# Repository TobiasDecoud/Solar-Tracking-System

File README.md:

# Solar-Tracking-System

Sistema que orienta automáticamente un panel solar hacia el sol a lo largo del día para maximizar la captación de energía.

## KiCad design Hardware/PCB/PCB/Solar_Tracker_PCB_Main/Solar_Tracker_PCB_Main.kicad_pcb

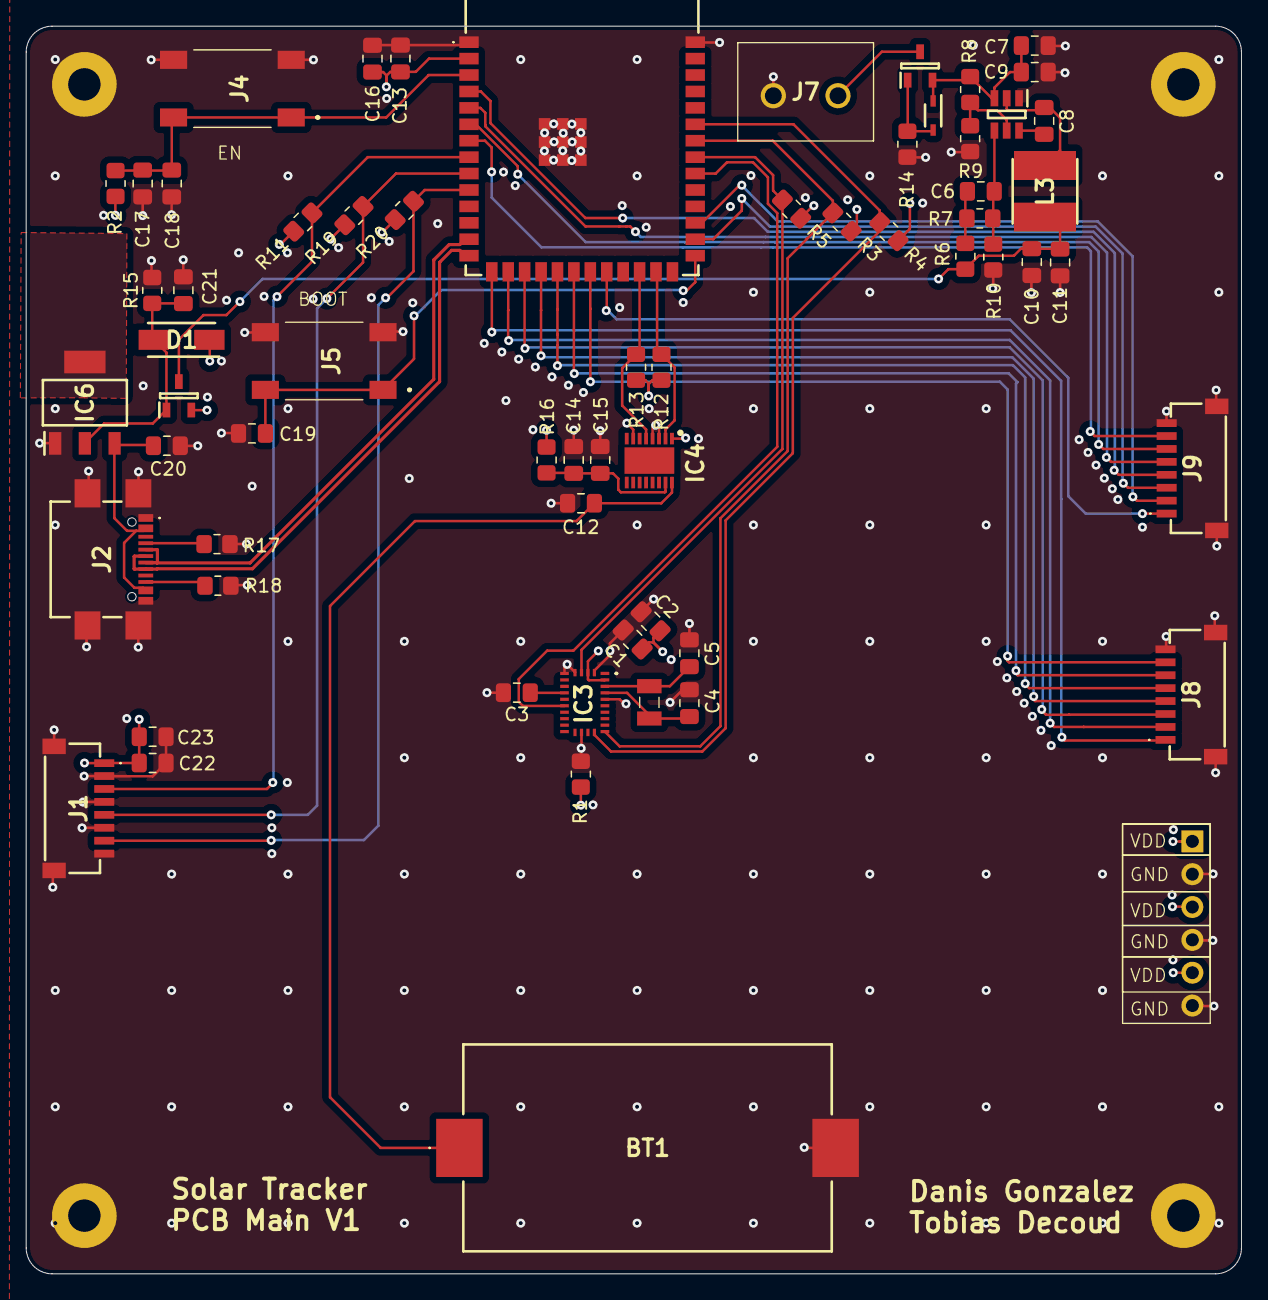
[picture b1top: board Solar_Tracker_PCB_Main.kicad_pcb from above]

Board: 4 copper layers, 94.0 x 96.5 mm, 67 parts (0 on the bottom side), 47 nets.

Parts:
BT1: BAT-HLD-013-SMT-TR; BATHLD013SMTTR
C1, C2, C8, C9, C16, C18, C19: 0.1u; C_0805_2012Metric_Pad1.18x1.45mm_HandSolder
C3, C12, C14, C23: 100n; C_0805_2012Metric_Pad1.18x1.45mm_HandSolder
C4, C5: 22p; C_0805_2012Metric_Pad1.18x1.45mm_HandSolder
C6: 47p; C_0805_2012Metric_Pad1.18x1.45mm_HandSolder
C7, C22: 10u; C_0805_2012Metric_Pad1.18x1.45mm_HandSolder
C10, C11, C13: 22u; C_0805_2012Metric_Pad1.18x1.45mm_HandSolder
C15, C17, C20: 1u; C_0805_2012Metric_Pad1.18x1.45mm_HandSolder
C21: 2.2u; C_0805_2012Metric_Pad1.18x1.45mm_HandSolder
D1: SBR2U30SA-13; DIOM5226X230N
H1, H2, H3, H4: MountingHole_Pad; MountingHole_2.5mm_Pad
IC1: ESP32-S3-WROOM-1-N4R8; ESP32S3WROOM1N4R8
IC2: TPS54302DDCT; SOT95P280X110-6N
IC3: BNO085
IC4: PCF2131TFY; SON50P350X450X150-17N-D
IC6: TLV76133DCYR; SOT230P700X180-4N
J1, J8, J9: SM08B-SRSS-TB_LF__SN_; SM08BSRSSTBLFSN
J2: USB4940-00-A; USB494000A
J3: Conn_01x06_Pin; PinHeader_1x06_P2.54mm_Vertical
J4, J5: 1977223-1; 19772231
J7: TB002-500-02BE; TB00250002BE
L3: 6.8u; INDPM5050X200N
Q1, Q2: DMP2045U-7; SOT96P240X115-3N
R1, R2, R5, R12, R13, R15: 10k; R_0805_2012Metric_Pad1.20x1.40mm_HandSolder
R3, R4: 4k; R_0805_2012Metric_Pad1.20x1.40mm_HandSolder
R6: 49.9; R_0805_2012Metric_Pad1.20x1.40mm_HandSolder
R7, R14: 100k; R_0805_2012Metric_Pad1.20x1.40mm_HandSolder
R8: 511k; R_0805_2012Metric_Pad1.20x1.40mm_HandSolder
R9: 105k; R_0805_2012Metric_Pad1.20x1.40mm_HandSolder
R10: 22.1k; R_0805_2012Metric_Pad1.20x1.40mm_HandSolder
R11, R19, R20: 4.7k; R_0805_2012Metric_Pad1.20x1.40mm_HandSolder
R16: 47k; R_0805_2012Metric_Pad1.20x1.40mm_HandSolder
R17, R18: 5.1k; R_0805_2012Metric_Pad1.20x1.40mm_HandSolder
Y1: 32.768kHz; ABS07
Z1: MM3Z5V6B; SODFL2512X90N

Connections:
+5V: C20.1, IC6.3 (IN), J2.A4 (VBUS_1), J2.B4 (VBUS_2)
/IMU/CAP: C3.1, IC3.9 (CAP)
/IMU/X_IN: C5.1, IC3.27 (XIN32), Y1.1
/IMU/X_OUT: C4.1, IC3.26 (XOUT32/CLKSEL1), Y1.2
/MCU/BOOT: C19.1, IC1.27 (IO0), J5.1 (COM_1), J5.2 (COM_2)
/MCU/EN: C17.1, C18.1, IC1.3 (EN), J4.1 (COM_1), J4.2 (COM_2), R2.2
/RTC/VBAT: BT1.1 (+), C12.2, IC4.16 (VBAT)
/RTC/VDD_IN: C14.2, C15.1, IC4.15 (VDD), R16.2
D+: IC1.14 (IO20), J2.A6 (DP1), J2.B6 (DP2)
D-: IC1.13 (IO19), J2.A7 (DN1), J2.B7 (DN2)
GND: BT1.2 (-), C1.2, C2.2, C3.2, C4.2, C5.2, C7.2, C9.2, C10.2, C11.1, C12.1, C13.2, C14.1, C15.2, C16.2, C17.2, C18.2, C19.2, C20.2, C21.2, C22.2, C23.2, H1.1, H2.1, H3.1, H4.1, IC1.1 (GND_1), IC1.40 (GND_2), IC1.41 (GND_3), IC1.42 (GND_4), IC1.43 (GND_5), IC1.44 (GND_6), IC1.45 (GND_7), IC1.46 (GND_8), IC1.47 (GND_9), IC1.48 (GND_10), IC1.49 (GND_11), IC2.1 (GND), IC3.2 (GND_1), IC3.5 (PS1), IC3.6 (PS0/WAKE), IC3.17 (SA0/H_MOSI_), IC3.25 (GND_2), IC4.3 (SDI), IC4.4 (SDO), IC4.7 (VSS), IC6.1 (GND), J1.2, J1.4, J1.6, J1.8, J1.9 (MP1), J1.10 (MP2), J2.A1 (GND_1), J2.B1 (GND_2), J2.S1 (GND_3), J2.S2 (GND_4), J2.S3 (GND_5), J2.S4 (GND_6), J3.2, J3.4, J3.6, J4.3 (NO_1), J4.4 (NO_2), J5.3 (NO_1), J5.4 (NO_2), J7.1, J8.8, J8.9 (MP1), J8.10 (MP2), J9.8, J9.9 (MP1), J9.10 (MP2), R1.2, R9.2, R10.2, R14.2, R15.2, R17.1, R18.2
IMU_BOOTN: IC1.33 (IO40), IC3.4 (BOOTN), R5.2
IMU_NRST: IC1.32 (IO39), IC3.11 (NRST)
IMU_SCL: IC1.35 (IO42), IC3.19 (H_SCL/SCK/RX), R4.2
IMU_SDA: IC1.34 (IO41), IC3.20 (H_SDA/H_MISO/TX_), R3.2
J1_2: IC1.21 (IO13), J8.7
J1_3: IC1.20 (IO12), J8.6
J1_4: IC1.19 (IO11), J8.5
J1_5: IC1.18 (IO10), J8.4
J1_6: IC1.17 (IO9), J8.3
J1_7: IC1.16 (IO46), J8.2
J1_8: IC1.15 (IO3), J8.1
J6_1: IC1.22 (IO14), J9.1
J6_2: IC1.29 (IO36), J9.2
J6_3: IC1.28 (IO35), J9.3
J6_4: IC1.4 (IO4), J9.4
J6_5: IC1.5 (IO5), J9.5
J6_6: IC1.6 (IO6), J9.6
J6_7: IC1.7 (IO7), J9.7
unnamed: C6.1, R6.2, R7.1
unnamed: C8.2, IC2.6 (BOOT)
unnamed: IC2.5 (EN), R8.2, R9.1
unnamed: C6.2, IC2.4 (FB), R7.2, R10.1
unnamed: C8.1, IC2.2 (SW), L3.1
unnamed: J2.A5 (CC1), R17.2
unnamed: J2.B5 (CC2), R18.1
unnamed: J7.2, Q1.3 (D)
unnamed: Q1.1 (G), R14.1, Z1.2 (A)
RTC_SCL: IC1.25 (IO48), IC4.2 (SCL), R12.2
RTC_SDA: IC1.24 (IO47), IC4.5 (SDA/~CE), R13.2
SL_INT: IC1.10 (IO17), J1.7, R20.2
SL_SCL: IC1.8 (IO15), J1.3, R11.2
SL_SDA: IC1.9 (IO16), J1.5, R19.2
Salida_protegida: C7.1, C9.1, IC2.3 (VIN), Q1.2 (S), R8.1, Z1.1 (K)
VDD: C1.1, C2.1, C13.1, C16.1, C22.1, C23.1, D1.1 (K), IC1.2 (3V3), IC3.3 (VDD), IC3.28 (VDDIO), IC4.1 (IFS), J1.1, J3.1, J3.3, J3.5, Q2.2 (S), R1.1, R2.1, R3.1, R4.1, R5.1, R11.1, R12.1, R13.1, R16.1, R19.1, R20.1
V_BUCK_BORNERA_3V3: C10.1, C11.2, L3.2, Q2.3 (D), R6.1
V_USB_3V3: C21.1, D1.2 (A), IC6.2 (OUT_1), Q2.1 (G), R15.1

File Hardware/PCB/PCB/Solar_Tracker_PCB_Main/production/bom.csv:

Designator,Footprint,Quantity,Value,LCSC Part #
BT1,BATHLD013SMTTR,1,BAT-HLD-013-SMT-TR,
"C1, C16, C18, C19, C2, C8, C9",0805,7,0.1u,
"C10, C11, C13",0805,3,22u,
"C12, C14, C3",0805,3,100n,
"C15, C17, C20",0805,3,1u,
C21,0805,1,2.2u,
"C22, C7",0805,2,10u,
"C4, C5",0805,2,22p,
C6,0805,1,47p,
D1,DIOM5226X230N,1,SBR2U30SA-13,
IC1,ESP32S3WROOM1N4R8,1,ESP32-S3-WROOM-1-N4R8,
IC2,SOT95P280X110-6N,1,TPS54302DDCT,
IC3,BNO085,1,BNO085,
IC4,SON50P350X450X150-17N-D,1,PCF2131TFY,
IC6,SOT230P700X180-4N,1,TLV76133DCYR,
"J1, J8, J9",SM08BSRSSTBLFSN,3,SM08B-SRSS-TB_LF__SN_,
J2,USB494000A,1,USB4940-00-A,
"J4, J5",19772231,2,1977223-1,
J7,TB00250002BE,1,TB002-500-02BE,
L3,INDPM5050X200N,1,6.8u,
"Q1, Q2",SOT96P240X115-3N,2,DMP2045U-7,
"R1, R12, R13, R15, R2, R5",0805,6,10k,
R10,0805,1,22.1k,
"R11, R19, R20",0805,3,4.7k,
"R14, R7",0805,2,100k,
R16,0805,1,47k,
"R17, R18",0805,2,5.1k,
"R3, R4",0805,2,4k,
R6,0805,1,49.9,
R8,0805,1,511k,
R9,0805,1,105k,
Y1,ABS07,1,32.768kHz,
Z1,SODFL2512X90N,1,MM3Z5V6B,

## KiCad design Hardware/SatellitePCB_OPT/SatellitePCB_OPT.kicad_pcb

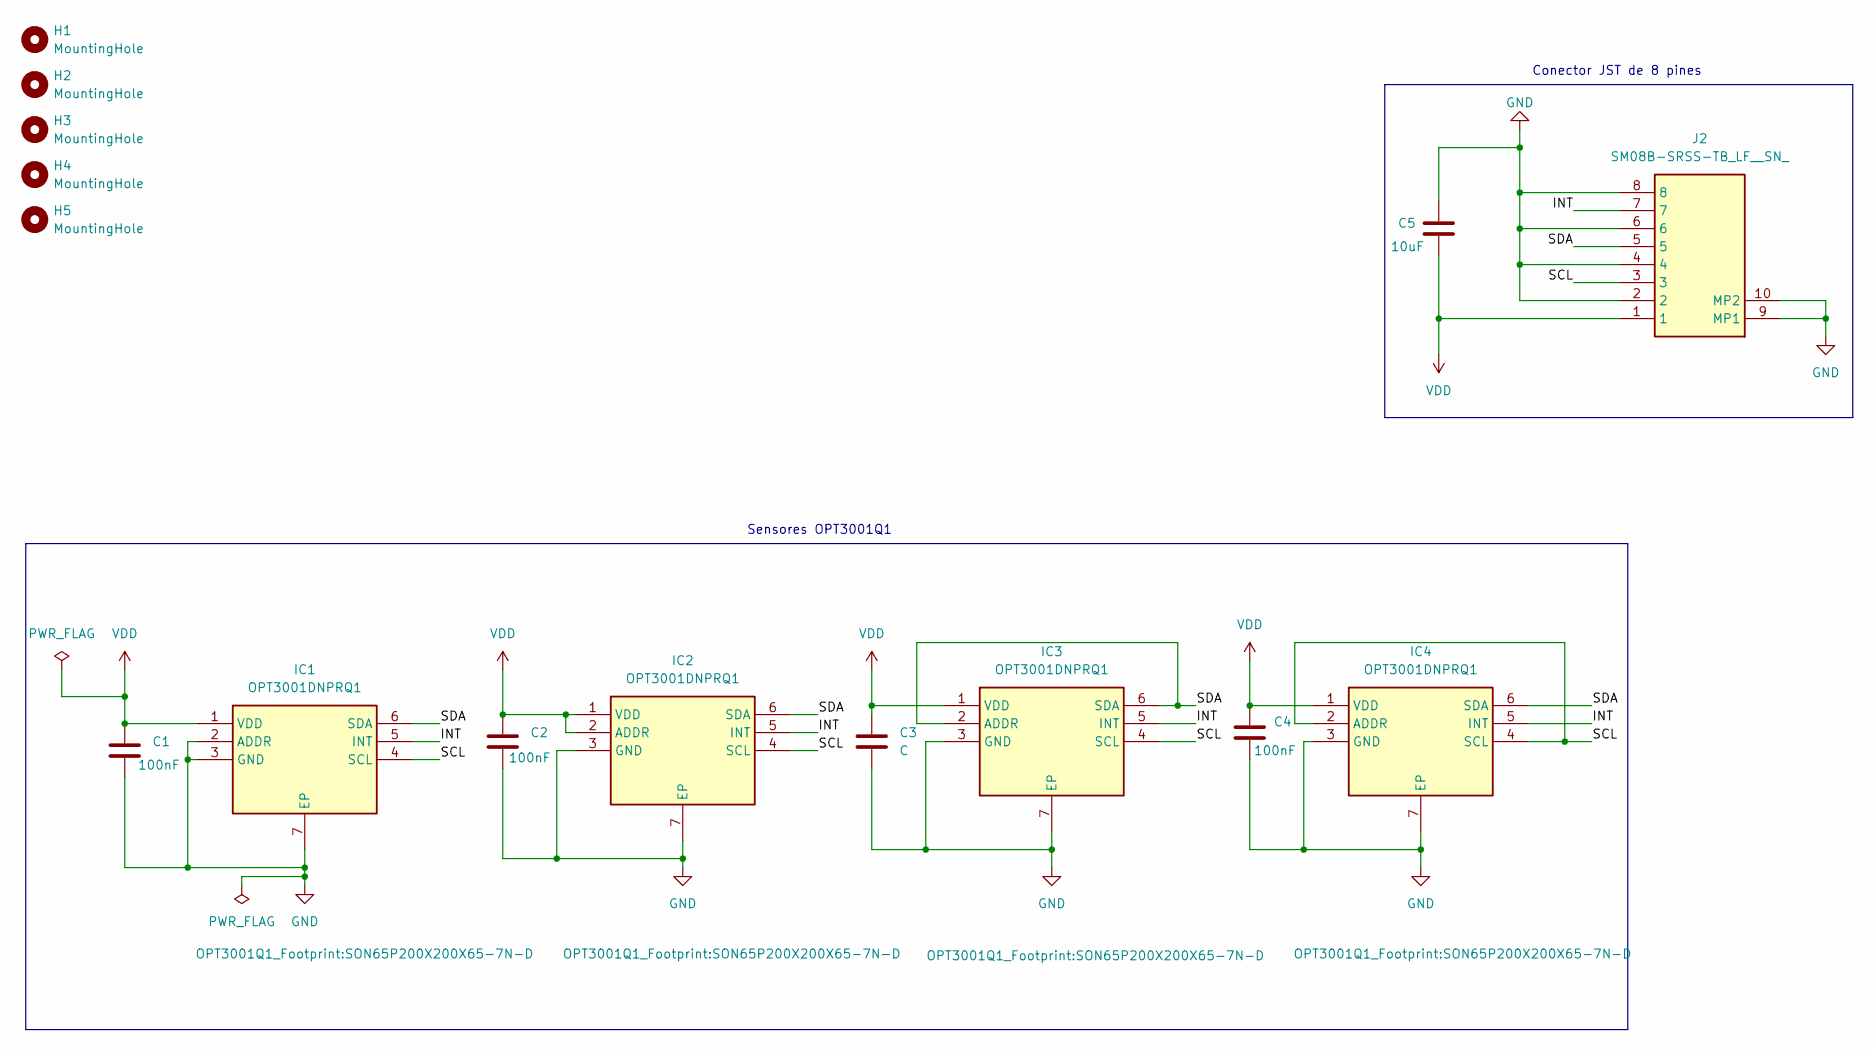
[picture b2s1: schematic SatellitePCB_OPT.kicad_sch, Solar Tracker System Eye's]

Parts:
C1, C2, C4: 100nF; C_0805_2012Metric_Pad1.18x1.45mm_HandSolder
C3: C; C_0805_2012Metric_Pad1.18x1.45mm_HandSolder
C5: 10uF; C_0805_2012Metric_Pad1.18x1.45mm_HandSolder
H1, H2, H3, H4, H5: MountingHole; MountingHole_2.2mm_M2
IC1, IC2, IC3, IC4: OPT3001DNPRQ1; SON65P200X200X65-7N-D; Mouser Part Number 595-OPT3001DNPRQ1
J2: SM08B-SRSS-TB_LF__SN_; SM08BSRSSTBLFSN; Mouser Part Number N/A

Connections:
/INT: IC1.5 (INT), IC2.5 (INT), IC3.5 (INT), IC4.5 (INT), J2.7
/SCL: IC1.4 (SCL), IC2.4 (SCL), IC3.4 (SCL), IC4.2 (ADDR), IC4.4 (SCL), J2.3
/SDA: IC1.6 (SDA), IC2.6 (SDA), IC3.2 (ADDR), IC3.6 (SDA), IC4.6 (SDA), J2.5
GND: C1.2, C2.2, C3.2, C4.2, C5.1, IC1.2 (ADDR), IC1.3 (GND), IC1.7 (EP), IC2.3 (GND), IC2.7 (EP), IC3.3 (GND), IC3.7 (EP), IC4.3 (GND), IC4.7 (EP), J2.2, J2.4, J2.6, J2.8, J2.9 (MP1), J2.10 (MP2)
VDD: C1.1, C2.1, C3.1, C4.1, C5.2, IC1.1 (VDD), IC2.1 (VDD), IC2.2 (ADDR), IC3.1 (VDD), IC4.1 (VDD), J2.1

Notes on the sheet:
Conector JST de 8 pines
Sensores OPT3001Q1

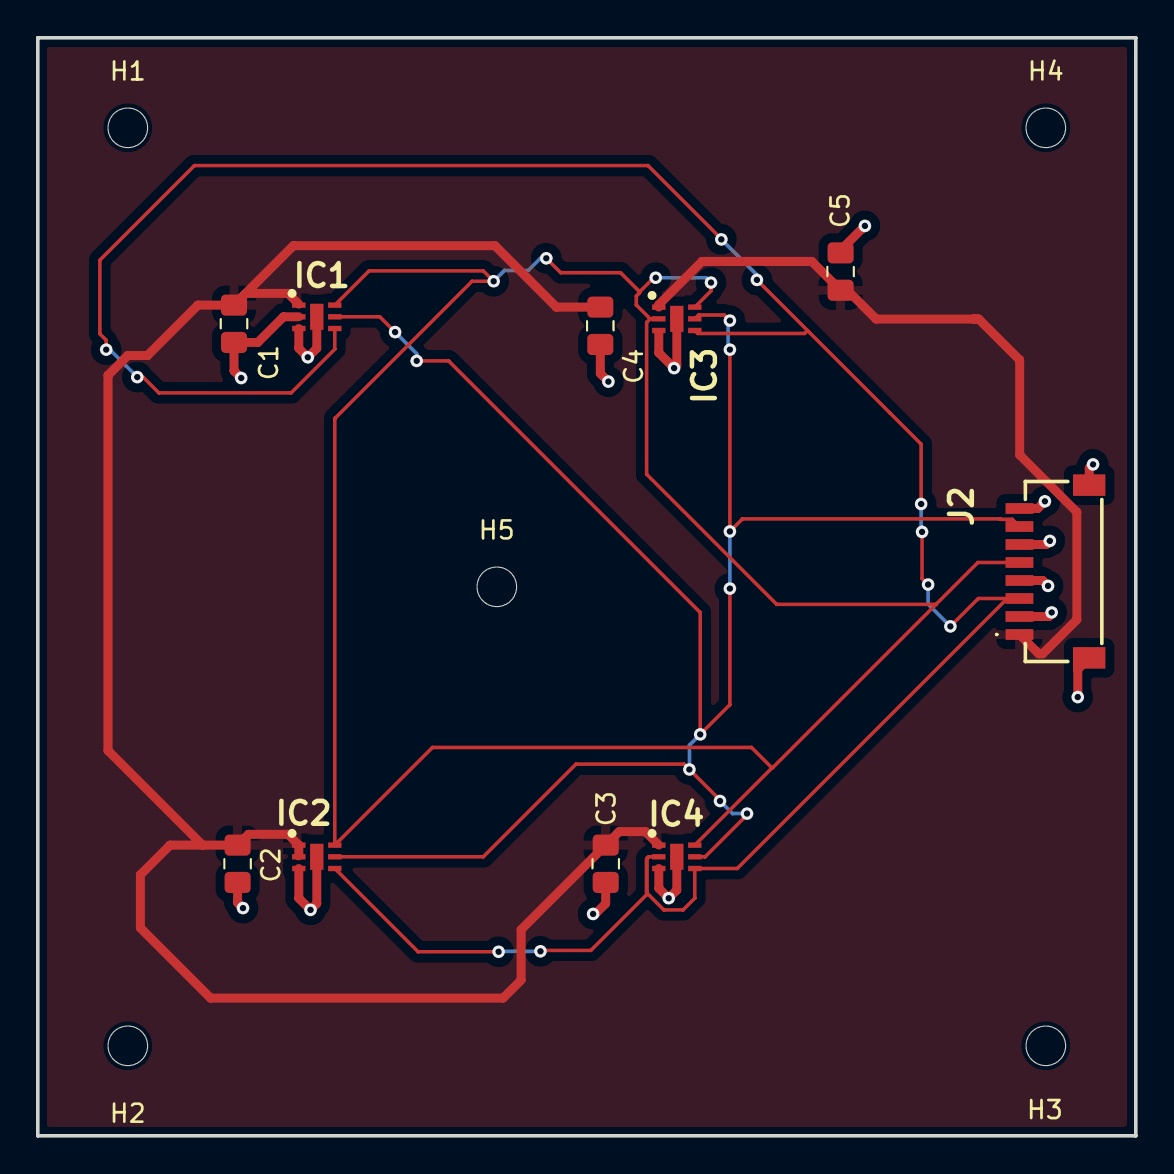
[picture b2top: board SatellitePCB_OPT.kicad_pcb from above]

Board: 2 copper layers, 61.0 x 61.0 mm, 15 parts (0 on the bottom side), 5 nets.

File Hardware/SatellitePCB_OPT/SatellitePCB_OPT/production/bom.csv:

Designator,Footprint,Quantity,Value,LCSC Part #
"C1, C2, C4",0805,3,100nF,
C3,0805,1,C,
C5,0805,1,10uF,
"IC1, IC2, IC3, IC4",SON65P200X200X65-7N-D,4,OPT3001DNPRQ1,
J2,SM08BSRSSTBLFSN,1,SM08B-SRSS-TB_LF__SN_,

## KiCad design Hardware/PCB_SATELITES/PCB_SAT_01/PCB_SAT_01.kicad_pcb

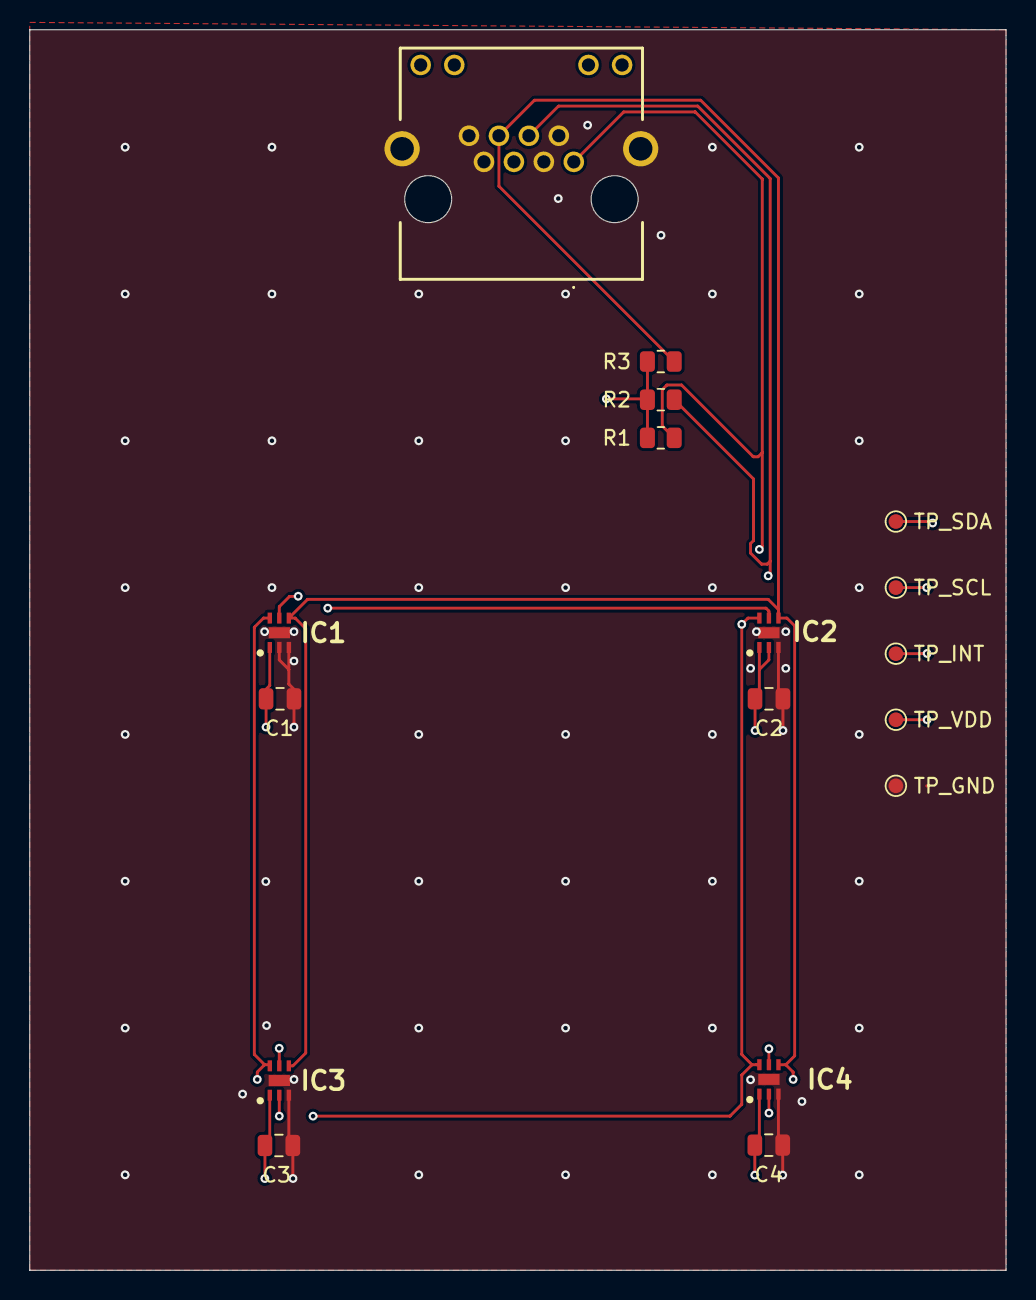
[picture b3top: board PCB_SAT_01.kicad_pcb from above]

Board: 4 copper layers, 66.5 x 84.5 mm, 17 parts (0 on the bottom side), 5 nets.

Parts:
C1, C2, C3, C4: 100n; C_0805_2012Metric
IC1, IC2, IC3, IC4: OPT3001DNPRQ1; SON65P200X200X65-7N-D
J1: MTJ-88ARX1-FSM-LG; MTJ88ARX1FSMLG
R1, R2, R3: 10k; R_0805_2012Metric
TP_GND: TestPoint; TestPoint_Pad_D1.0mm
TP_INT: TestPoint; TestPoint_Pad_D1.0mm
TP_SCL: TestPoint; TestPoint_Pad_D1.0mm
TP_SDA: TestPoint; TestPoint_Pad_D1.0mm
TP_VDD: TestPoint; TestPoint_Pad_D1.0mm

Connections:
/INT: IC1.5 (INT), IC2.5 (INT), IC3.5 (INT), IC4.5 (INT), J1.4, R2.2, TP_INT.1
/SCL: IC1.4 (SCL), IC2.4 (SCL), IC3.4 (SCL), IC4.2 (ADDR), IC4.4 (SCL), J1.6, R3.2, TP_SCL.1
/SDA: IC1.6 (SDA), IC2.6 (SDA), IC3.2 (ADDR), IC3.6 (SDA), IC4.6 (SDA), J1.1, R1.2, TP_SDA.1
GND: C1.2, C2.2, C3.2, C4.2, IC1.2 (ADDR), IC1.3 (GND), IC1.7 (EP), IC2.3 (GND), IC2.7 (EP), IC3.3 (GND), IC3.7 (EP), IC4.3 (GND), IC4.7 (EP), J1.2, J1.3, J1.7, J1.8, J1.MH1, J1.MH2, TP_GND.1
VDD: C1.1, C2.1, C3.1, C4.1, IC1.1 (VDD), IC2.1 (VDD), IC2.2 (ADDR), IC3.1 (VDD), IC4.1 (VDD), J1.5, R1.1, R2.1, R3.1, TP_VDD.1

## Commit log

2026-02-14 Create hw
2026-02-14 Create Esquemático
2026-02-14 Create Codigo
2026-02-14 Añadido Esquematico_V01.drawio
2026-02-14 Añadido Esquematico_V01.drawio.png
2026-02-20 prueba
2026-02-21 Update Codigo
2026-02-21 Añadido Esquematico_P3.drawio.svg
2026-02-21 Actualizar Esquematico_P3.drawio.svg
2026-02-21 Update README with project details and requirements
    Added detailed project description and requirements for the solar tracking system.
2026-02-21 Remove project details from README.md
    Removed detailed project description and hardware requirements from README.
2026-02-21 hola
2026-02-22 Actualizacion del README
2026-02-24 Añadir Fuentes
2026-02-25 Creacion del archivo para el PCB MAIN
2026-02-25 Actuaizacion PCB
2026-02-26 Agregue el sensor
2026-02-26 Tobi Gay
2026-02-26 Ejemplo Elevacion y Azimut
2026-02-28 Actualizacion PCB
2026-02-28 anhadir pcb satelite 01
2026-03-01 Actualizacion de PCB Satelite 01
2026-03-02 Actualizacion PCB SATELITE 1
2026-03-03 actualizacion pcb satelite
2026-03-03 actualizacion de pcb (IMU)
2026-03-04 actualizacion pcb main
2026-03-06 Actualizacion PCB Principal
2026-03-06 actualizacion de pcb
2026-03-08 Eliminacion de la Bibliografia
2026-03-09 Bibliografía
2026-03-10 Actualizacion de Footprints Resistencias y Capacitores Main PCB
2026-03-10 Actualizacion de PCB Main
2026-03-10 Anhadir Footprint USBC
2026-03-11 Puerto USB con Regulador
2026-03-11 Actualizacion Main pcb
2026-03-11 actualizacion
2026-03-11 Bornera
2026-03-12 Calculo de resistencias PullUp para la placa Satelite
2026-03-12 comienzo de distribucion pcb
2026-03-12 Colocacion de los componentes en el PCB
2026-03-12 PCB ruteado
2026-03-12 pcb main actualizacion
2026-03-13 Modificaciones PCB MAIN
2026-03-13 Satellite PCB for a Solar Tracker System
    Este PCB contiene los sensores que serán los "ojos" del proyecto.
2026-03-16 Cambios recomendados por el profe
2026-03-16 Archivo Gerber
2026-03-16 Confi del par diferencial
2026-03-16 Par deferencial
2026-03-16 Agregue cotas
2026-03-17 Cambios Menores
2026-03-17 Agregue vias GND cerca de las vias VDD
2026-03-18 Versión final del PCB Satélite
2026-03-18 Agregar tierra a las Borneras
2026-03-19 Nuevo conector JST
2026-03-20 Agregue conectores JST
2026-03-20 Agregue bias por todos lados
2026-03-20 Agregue protecciones de polaridad inversa y independencia de fuentes
2026-03-21 Delete Hardware/SatellitePCB_OPT directory
    Hay que cambiar la bornera por conectores JST
2026-03-21 Versión final del PCB Satélite con conector JST
    Se procedió a cambiar la bornera por un conector JST
2026-03-21 Agregue Esquematico General
2026-03-21 Actualizar Diagrama sin título.drawio
2026-03-21 Añadido Esquematico General.svg
2026-03-21 Actualizar Esquematico General.svg
2026-03-28 Subi pcb main arreglado 100%
2026-03-28 vias mas grandes
2026-03-28 Actualizacion de PCB Satelite
2026-03-29 agregue lista de compras
2026-03-29 elimine diagrama anterior
2026-03-30 Actualizacion menor
2026-04-12 Cambios, disminuir vias, pads en vdd
2026-04-13 Agregue pines vdd y gnd
2026-04-18 cambios pcb main
2026-04-18 Actualizacion capactiores desacoplo hacia placa satelite
2026-04-18 cambios main
2026-04-23 Creacion Gerber
2026-05-20 Correccion del esquematico BUCK
2026-05-20 Correccion BUCK
2026-05-30 Agregue proyecto3_v2
2026-05-30 Actualizacion codigo
2026-05-30 actualizacion software
2026-05-30 Arreglo PBS
2026-05-31 Agregue flujo general
